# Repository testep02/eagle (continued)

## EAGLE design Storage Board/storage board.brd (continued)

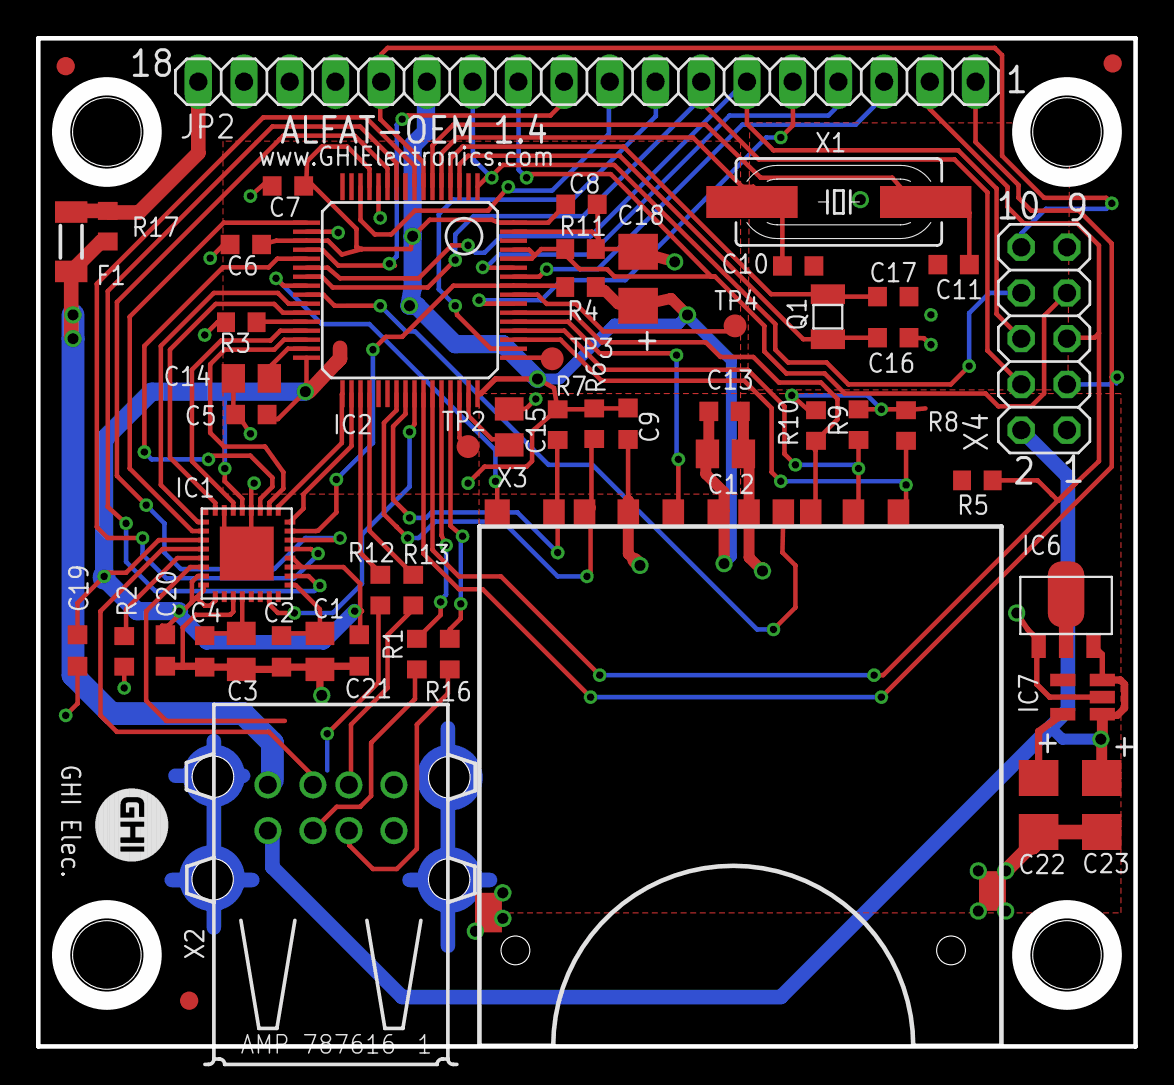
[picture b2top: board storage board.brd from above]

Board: 2 copper layers, 61.0 x 56.0 mm, 55 parts (0 on the bottom side), 59 nets.

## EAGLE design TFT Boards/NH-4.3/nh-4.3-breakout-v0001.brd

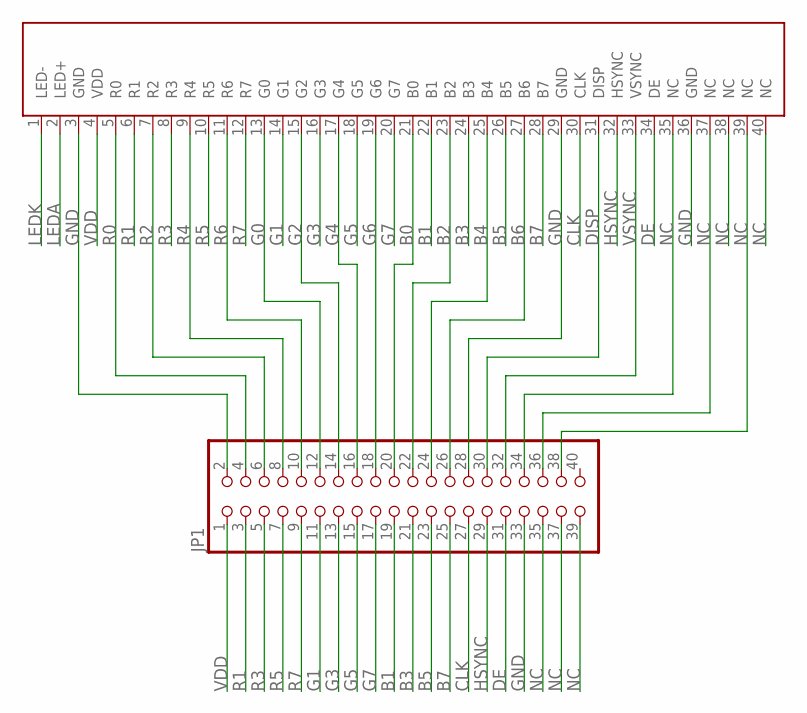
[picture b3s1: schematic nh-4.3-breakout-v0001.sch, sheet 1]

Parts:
JP1: PINHD-2X20; 2X20
U$1: NH-4.3; FPC-40

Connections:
B0: JP1.20, U$1.21 (B0)
B1: JP1.19, U$1.22 (B1)
B2: JP1.22, U$1.23 (B2)
B3: JP1.21, U$1.24 (B3)
B4: JP1.24, U$1.25 (B4)
B5: JP1.23, U$1.26 (B5)
B6: JP1.26, U$1.27 (B6)
B7: JP1.25, U$1.28 (B7)
CLK: JP1.27, U$1.30 (CLK)
DE: JP1.31, U$1.34 (DE)
DISP: JP1.30, U$1.31 (DISP)
G0: JP1.12, U$1.13 (G0)
G1: JP1.11, U$1.14 (G1)
G2: JP1.14, U$1.15 (G2)
G3: JP1.13, U$1.16 (G3)
G4: JP1.16, U$1.17 (G4)
G5: JP1.15, U$1.18 (G5)
G6: JP1.18, U$1.19 (G6)
G7: JP1.17, U$1.20 (G7)
GND: JP1.2, JP1.28, JP1.33, U$1.3 (GND), U$1.29 (GND), U$1.36 (GND); also elsewhere on the board
HSYNC: JP1.29, U$1.32 (HSYNC)
LEDA: U$1.2 (LED+); also elsewhere on the board
LEDK: U$1.1 (LED-); also elsewhere on the board
NC: JP1.34, JP1.35, JP1.36, JP1.37, JP1.38, JP1.39, U$1.35 (NC), U$1.37 (NC), U$1.38 (NC), U$1.39 (NC), U$1.40 (NC)
R0: JP1.4, U$1.5 (R0)
R1: JP1.3, U$1.6 (R1)
R2: JP1.6, U$1.7 (R2)
R3: JP1.5, U$1.8 (R3)
R4: JP1.8, U$1.9 (R4)
R5: JP1.7, U$1.10 (R5)
R6: JP1.10, U$1.11 (R6)
R7: JP1.9, U$1.12 (R7)
VDD: JP1.1, U$1.4 (VDD)
VSYNC: JP1.32, U$1.33 (VSYNC)

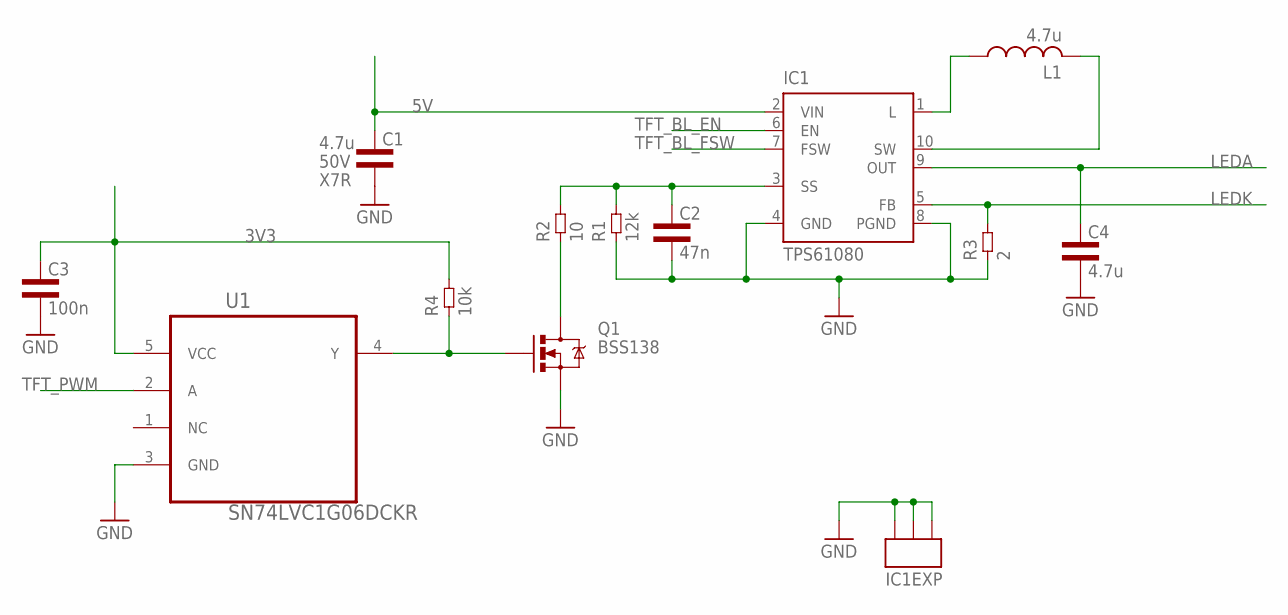
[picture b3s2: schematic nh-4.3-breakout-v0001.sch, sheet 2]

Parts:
C1: 4.7u; 1210L3; VOLTAGE 50V
C2: 47n; 0603L3
C3: 100n; 0603L3
C4: 4.7u; 1210L3
IC1: TPS61080; S-PDSO-N10
L1: 4.7u; RCL_VLCF4018-2
Q1: MOSFET-NCHANNELBSS138; SOT23
R1: 12k; 0603L3
R2: 10; 0603L3
R3: 2; 1210L3
R4: 10k; 0603L3
U1: SN74LVC1G06DCKR; SOT65P210X110-5N

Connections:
3V3: C3.P$1 (1), R4.P$2 (2), U1.5 (VCC)
5V: C1.P$1 (1), IC1.2 (VIN)
GND: C1.P$2 (2), C2.P$2 (2), C3.P$2 (2), C4.P$2 (2), IC1.4 (GND), IC1.8 (PGND), IC1.PP (EXP), IC1.PP@1 (EXP), IC1.PP@2 (EXP), Q1.2 (S), R1.P$1 (1), R3.P$1 (1), U1.3 (GND); also elsewhere on the board
LEDA: C4.P$1 (1), IC1.9 (OUT); also elsewhere on the board
LEDK: IC1.5 (FB), R3.P$2 (2); also elsewhere on the board
unnamed: C2.P$1 (1), IC1.3 (SS), R1.P$2 (2), R2.P$2 (2)
unnamed: Q1.3 (D), R2.P$1 (1)
unnamed: IC1.10 (SW), L1.2
unnamed: IC1.1 (L), L1.1
TFT_BL_EN: IC1.6 (EN)
TFT_BL_FSW: IC1.7 (FSW)
TFT_PWM: U1.2 (A)
Y: Q1.1 (G), R4.P$1 (1), U1.4 (Y)

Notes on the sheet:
BSS138

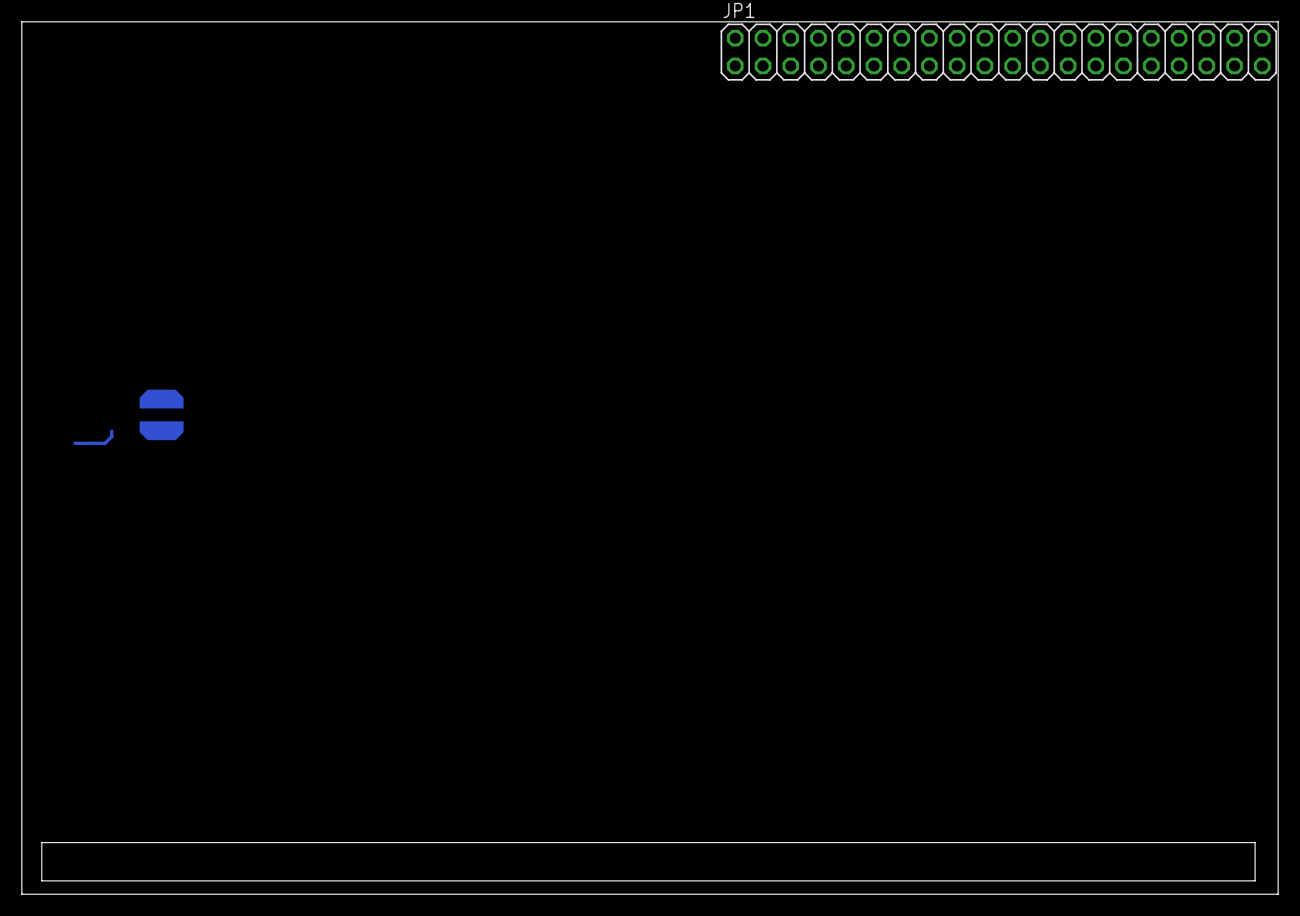
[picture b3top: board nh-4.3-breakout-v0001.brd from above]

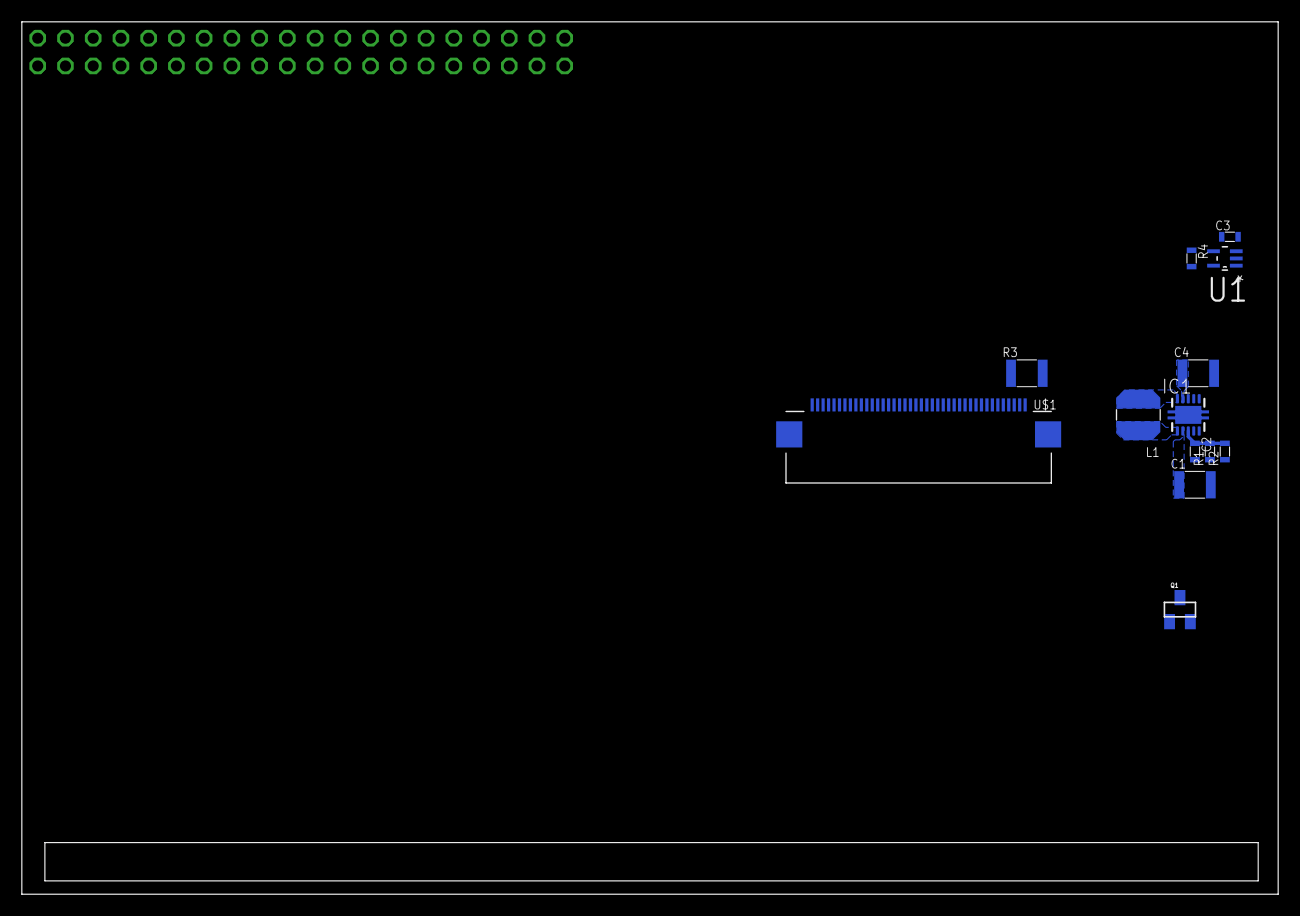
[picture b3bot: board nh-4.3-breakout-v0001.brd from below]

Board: 2 copper layers, 115.0 x 79.9 mm, 14 parts (13 on the bottom side), 41 nets.

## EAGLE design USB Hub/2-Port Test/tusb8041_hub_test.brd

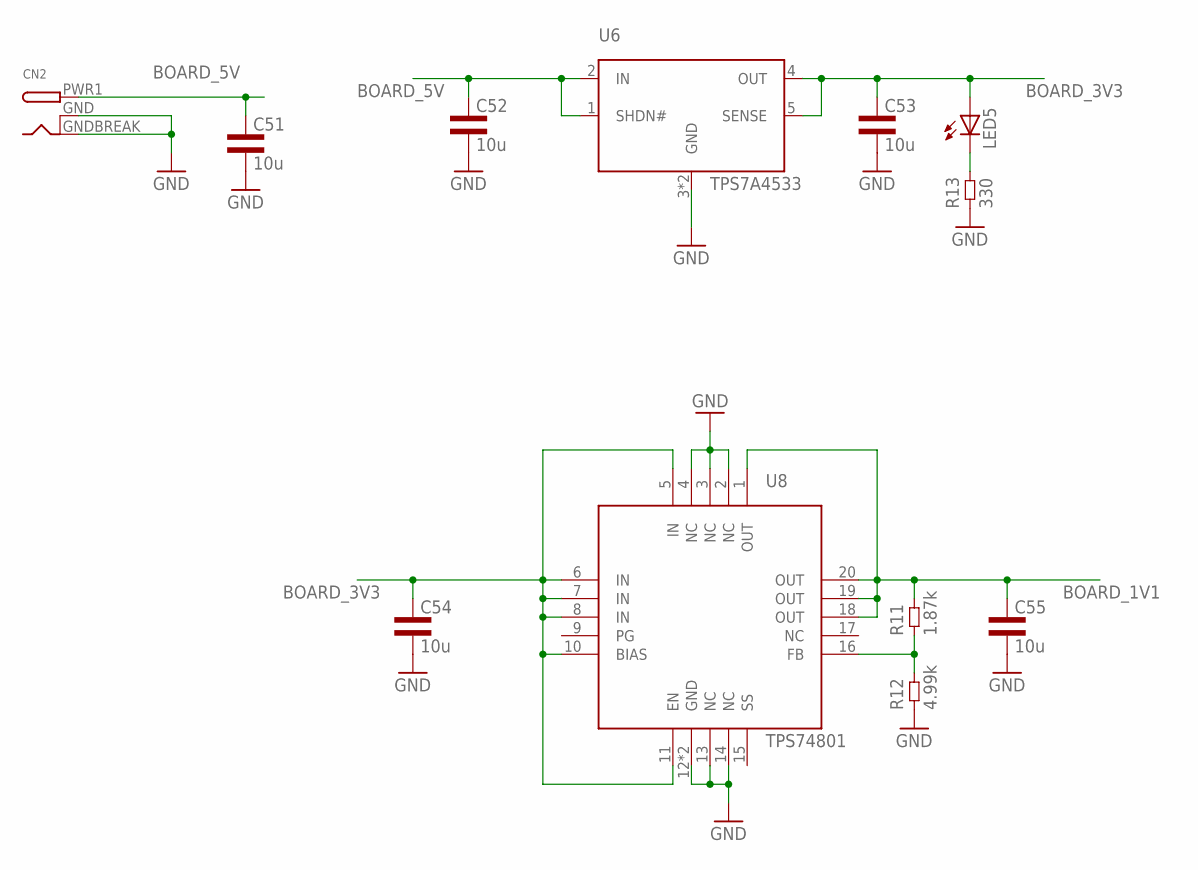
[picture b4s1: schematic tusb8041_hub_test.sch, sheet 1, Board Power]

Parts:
C51, C52, C53, C54, C55: 10u; 1206L3
CN2: DCBARRELSMT; DCJACK_2MM_SMT
LED5: LEDCHIP-LED0603; CHIP-LED0603
R11: 1.87k; 0402L3
R12: 4.99k; 0402L3
R13: 330; 0603L3
U6: TPS7A4533; R-PSFM-G5
U8: TPS74801; S-PVQFN-N20

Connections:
BOARD_1V1: C55.1, R11.P$2 (2), U8.1 (OUT), U8.18 (OUT), U8.19 (OUT), U8.20 (OUT); also elsewhere on the board
BOARD_3V3: C53.1, C54.1, LED5.A, U6.4 (OUT), U6.5 (SENSE), U8.5 (IN), U8.6 (IN), U8.7 (IN), U8.8 (IN), U8.10 (BIAS), U8.11 (EN); also elsewhere on the board
BOARD_5V: C51.1, C52.1, CN2.PWR1 (PWR), U6.1 (SHDN#), U6.2 (IN); also elsewhere on the board
GND: C51.2, C52.2, C53.2, C54.2, C55.2, CN2.GND (GNDBREAK), CN2.GNDBREAK (GND), R12.P$1 (1), R13.P$1 (1), U6.3 (GND), U6.TP (GND), U8.2 (NC), U8.3 (NC), U8.4 (NC), U8.12 (GND), U8.13 (NC), U8.14 (NC), U8.TP (GND); also elsewhere on the board
unnamed: LED5.C, R13.P$2 (2)
unnamed: R11.P$1 (1), R12.P$2 (2), U8.16 (FB)

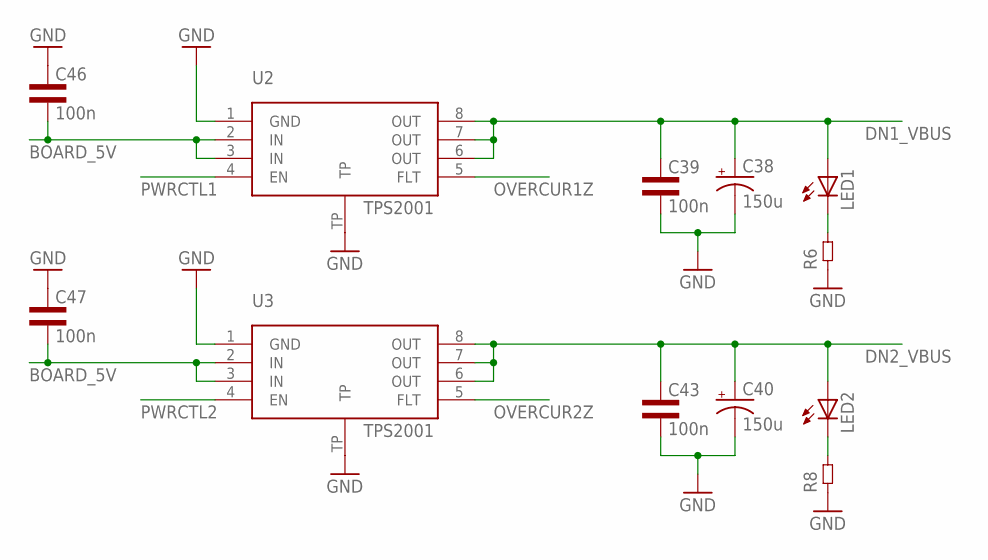
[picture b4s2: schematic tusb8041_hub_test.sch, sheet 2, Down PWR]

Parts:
C38, C40: 150u; CT7343
C39, C43, C46, C47: 100n; 0603L3
LED1, LED2: LEDCHIP-LED0603; CHIP-LED0603
R6, R8: RES0603L3; 0603L3
U2, U3: TPS2001; S-PDSO-G8

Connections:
BOARD_5V: C46.P$2 (2), C47.P$2 (2), U2.2 (IN), U2.3 (IN), U3.2 (IN), U3.3 (IN); also elsewhere on the board
DN1_VBUS: C38.+, C39.P$1 (1), LED1.A, U2.6 (OUT), U2.7 (OUT), U2.8 (OUT); also elsewhere on the board
DN2_VBUS: C40.+, C43.P$1 (1), LED2.A, U3.6 (OUT), U3.7 (OUT), U3.8 (OUT); also elsewhere on the board
GND: C38.-, C39.P$2 (2), C40.-, C43.P$2 (2), C46.P$1 (1), C47.P$1 (1), R6.P$1 (1), R8.P$1 (1), U2.1 (GND), U2.TP, U3.1 (GND), U3.TP; also elsewhere on the board
unnamed: LED1.C, R6.P$2 (2)
unnamed: LED2.C, R8.P$2 (2)
OVERCUR1Z: U2.5 (FLT); also elsewhere on the board
OVERCUR2Z: U3.5 (FLT); also elsewhere on the board
PWRCTL1: U2.4 (EN); also elsewhere on the board
PWRCTL2: U3.4 (EN); also elsewhere on the board

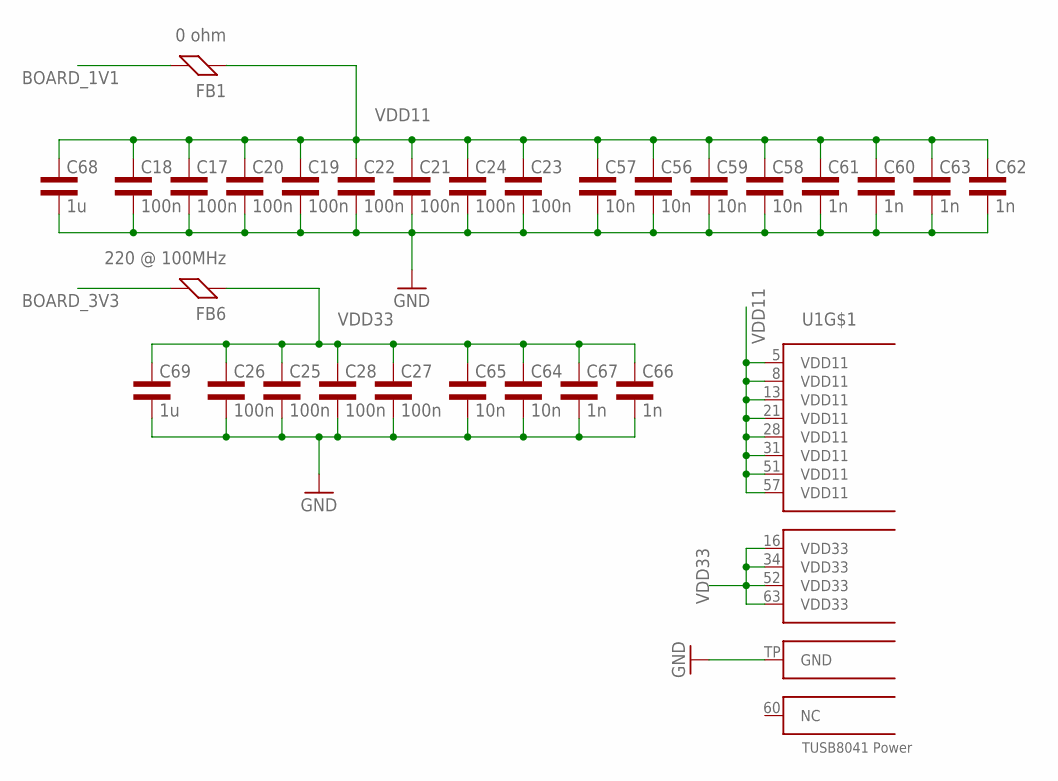
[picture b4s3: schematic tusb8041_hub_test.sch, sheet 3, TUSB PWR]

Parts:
C17, C18, C19, C20, C21, C22, C23, C24, C25, C26, C27, C28: 100n; 0402L3
C56, C57, C58, C59, C64, C65: 10n; 0402L3
C60, C61, C62, C63, C66, C67: 1n; 0402L3
C68, C69: 1u; 0805L3
FB1: 0 ohm; 0603L3
FB6: 220 @ 100MHz; 0603L3
U1: TUSB8041; VQFN64

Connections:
BOARD_1V1: FB1.P$2 (2); also elsewhere on the board
BOARD_3V3: FB6.P$2 (2); also elsewhere on the board
GND: C17.P$2 (2), C18.P$2 (2), C19.P$2 (2), C20.P$2 (2), C21.P$2 (2), C22.P$2 (2), C23.P$2 (2), C24.P$2 (2), C25.P$2 (2), C26.P$2 (2), C27.P$2 (2), C28.P$2 (2), C56.P$2 (2), C57.P$2 (2), C58.P$2 (2), C59.P$2 (2), C60.P$2 (2), C61.P$2 (2), C62.P$2 (2), C63.P$2 (2), C64.P$2 (2), C65.P$2 (2), C66.P$2 (2), C67.P$2 (2), C68.2, C69.2, U1.TP (GND); also elsewhere on the board
VDD11: C17.P$1 (1), C18.P$1 (1), C19.P$1 (1), C20.P$1 (1), C21.P$1 (1), C22.P$1 (1), C23.P$1 (1), C24.P$1 (1), C56.P$1 (1), C57.P$1 (1), C58.P$1 (1), C59.P$1 (1), C60.P$1 (1), C61.P$1 (1), C62.P$1 (1), C63.P$1 (1), C68.1, FB1.P$1 (1), U1.5 (VDD11), U1.8 (VDD11), U1.13 (VDD11), U1.21 (VDD11), U1.28 (VDD11), U1.31 (VDD11), U1.51 (VDD11), U1.57 (VDD11)
VDD33: C25.P$1 (1), C26.P$1 (1), C27.P$1 (1), C28.P$1 (1), C64.P$1 (1), C65.P$1 (1), C66.P$1 (1), C67.P$1 (1), C69.1, FB6.P$1 (1), U1.16 (VDD33), U1.34 (VDD33), U1.52 (VDD33), U1.63 (VDD33); also elsewhere on the board

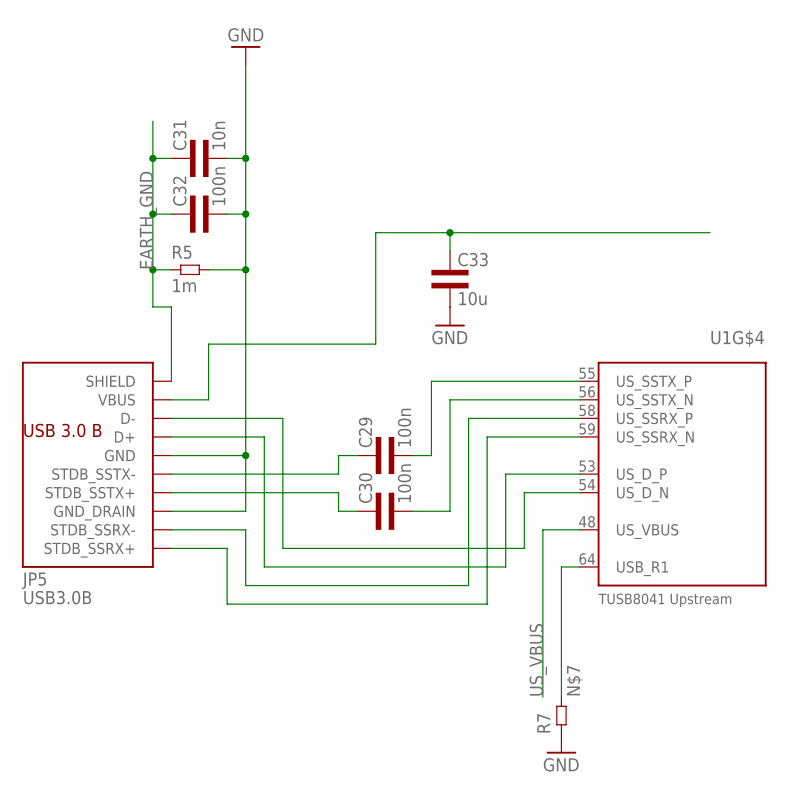
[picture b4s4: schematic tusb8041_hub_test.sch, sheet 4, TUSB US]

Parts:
C29, C30: 100n; 0402L3
C31: 10n; 0603L3
C32: 100n; 0603L3
C33: 10u; 1206L3
JP5: USB3.0B; AMPHENOLUSB3.0B
R5: 1m; 0603L3
R7: RES0402L3; 0402L3
U1: TUSB8041; VQFN64

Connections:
EARTH_GND: C31.P$1 (1), C32.P$1 (1), JP5.10@1 (SHIELD), JP5.10@2 (SHIELD), R5.P$1 (1); also elsewhere on the board
GND: C31.P$2 (2), C32.P$2 (2), C33.2, JP5.4 (GND), JP5.7 (GND_DRAIN), R5.P$2 (2), R7.P$1 (1); also elsewhere on the board
unnamed: R7.P$2 (2), U1.64 (USB_R1)
US_CAP_SSTX_N: C29.P$1 (1), JP5.5 (STDB_SSTX-)
US_CAP_SSTX_P: C30.P$1 (1), JP5.6 (STDB_SSTX+)
US_D_N: JP5.2 (D-), U1.54 (US_D_N)
US_D_P: JP5.3 (D+), U1.53 (US_D_P)
US_SSRX_N: JP5.9 (STDB_SSRX+), U1.59 (US_SSRX_N)
US_SSRX_P: JP5.8 (STDB_SSRX-), U1.58 (US_SSRX_P)
US_SSTX_N: C30.P$2 (2), U1.56 (US_SSTX_N)
US_SSTX_P: C29.P$2 (2), U1.55 (US_SSTX_P)
US_VBUS: C33.1, JP5.1 (VBUS), U1.48 (US_VBUS)

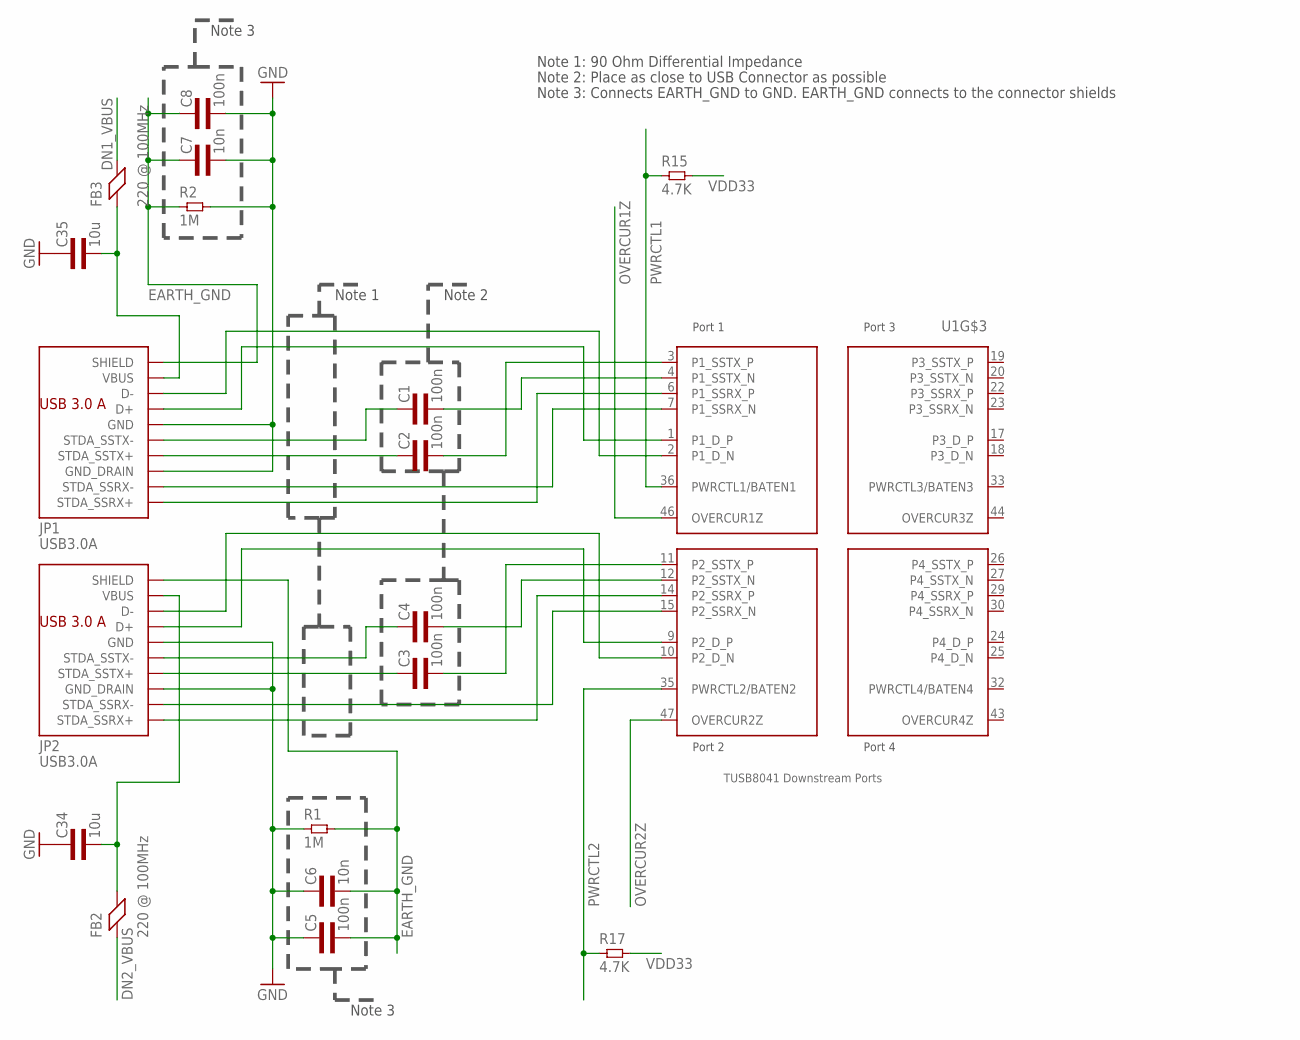
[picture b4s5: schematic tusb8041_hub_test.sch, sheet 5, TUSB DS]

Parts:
C1, C2, C3, C4: 100n; 0402L3
C5, C8: 100n; 0603L3
C6, C7: 10n; 0603L3
C34, C35: 10u; 1206L3
FB2, FB3: 220 @ 100MHz; 0603L1
JP1, JP2: USB3.0A; AMPHENOLUSB3.0A
R1, R2: 1M; 0603L3
R15, R17: 4.7K; 0402L3
U1: TUSB8041; VQFN64

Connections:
DN1_VBUS: FB3.2; also elsewhere on the board
DN2_VBUS: FB2.1; also elsewhere on the board
EARTH_GND: C5.P$2 (2), C6.P$2 (2), C7.P$1 (1), C8.P$1 (1), JP1.10@1 (SHIELD), JP1.10@2 (SHIELD), JP2.10@1 (SHIELD), JP2.10@2 (SHIELD), R1.P$2 (2), R2.P$1 (1); also elsewhere on the board
GND: C5.P$1 (1), C6.P$1 (1), C7.P$2 (2), C8.P$2 (2), C34.1, C35.1, JP1.4 (GND), JP1.7 (GND_DRAIN), JP2.4 (GND), JP2.7 (GND_DRAIN), R1.P$1 (1), R2.P$2 (2); also elsewhere on the board
unnamed: C35.2, FB3.1, JP1.1 (VBUS)
unnamed: C34.2, FB2.2, JP2.1 (VBUS)
OVERCUR1Z: U1.46 (OVERCUR1Z); also elsewhere on the board
OVERCUR2Z: U1.47 (OVERCUR2Z); also elsewhere on the board
P1_CAP_SSTX_N: C1.P$1 (1), JP1.8 (STDA_SSTX-)
P1_CAP_SSTX_P: C2.P$1 (1), JP1.9 (STDA_SSTX+)
P1_D_N: JP1.2 (D-), U1.2 (P1_D_N)
P1_D_P: JP1.3 (D+), U1.1 (P1_D_P)
P1_SSRX_N: JP1.5 (STDA_SSRX-), U1.7 (P1_SSRX_N)
P1_SSRX_P: JP1.6 (STDA_SSRX+), U1.6 (P1_SSRX_P)
P1_SSTX_N: C1.P$2 (2), U1.4 (P1_SSTX_N)
P1_SSTX_P: C2.P$2 (2), U1.3 (P1_SSTX_P)
P2_CAP_SSTX_N: C4.P$1 (1), JP2.8 (STDA_SSTX-)
P2_CAP_SSTX_P: C3.P$1 (1), JP2.9 (STDA_SSTX+)
P2_D_N: JP2.2 (D-), U1.10 (P2_D_N)
P2_D_P: JP2.3 (D+), U1.9 (P2_D_P)
P2_SSRX_N: JP2.5 (STDA_SSRX-), U1.15 (P2_SSRX_N)
P2_SSRX_P: JP2.6 (STDA_SSRX+), U1.14 (P2_SSRX_P)
P2_SSTX_N: C4.P$2 (2), U1.12 (P2_SSTX_N)
P2_SSTX_P: C3.P$2 (2), U1.11 (P2_SSTX_P)
PWRCTL1: R15.P$1 (1), U1.36 (PWRCTL1/BATEN1); also elsewhere on the board
PWRCTL2: R17.P$1 (1), U1.35 (PWRCTL2/BATEN2); also elsewhere on the board
VDD33: R15.P$2 (2), R17.P$2 (2); also elsewhere on the board

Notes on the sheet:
Note 1
Note 2
Note 3
Note 1: 90 Ohm Differential Impedance
Note 2: Place as close to USB Connector as possible
Note 3: Connects EARTH_GND to GND. EARTH_GND connects to the connector shields

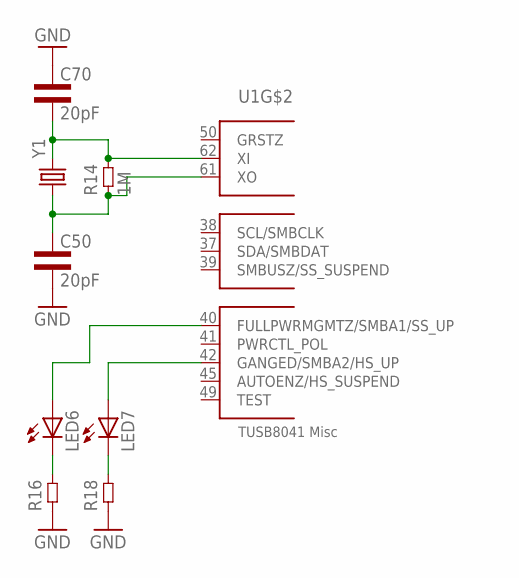
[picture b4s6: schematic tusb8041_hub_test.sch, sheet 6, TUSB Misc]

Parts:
C50, C70: 20pF; 0402L3
LED6, LED7: LEDCHIPLED_0603; CHIPLED_0603
R14: 1M; 0402L3
R16, R18: RES0402L3; 0402L3
U1: TUSB8041; VQFN64
Y1: CRYSTALHC49US; HC49US

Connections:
CLK_N: C70.P$2 (2), R14.P$2 (2), U1.62 (XI), Y1.2
CLK_P: C50.P$1 (1), R14.P$1 (1), U1.61 (XO), Y1.1
GND: C50.P$2 (2), C70.P$1 (1), R16.P$1 (1), R18.P$1 (1); also elsewhere on the board
unnamed: LED6.C, R16.P$2 (2)
unnamed: LED7.C, R18.P$2 (2)
unnamed: LED7.A, U1.42 (GANGED/SMBA2/HS_UP)
unnamed: LED6.A, U1.40 (FULLPWRMGMTZ/SMBA1/SS_UP)

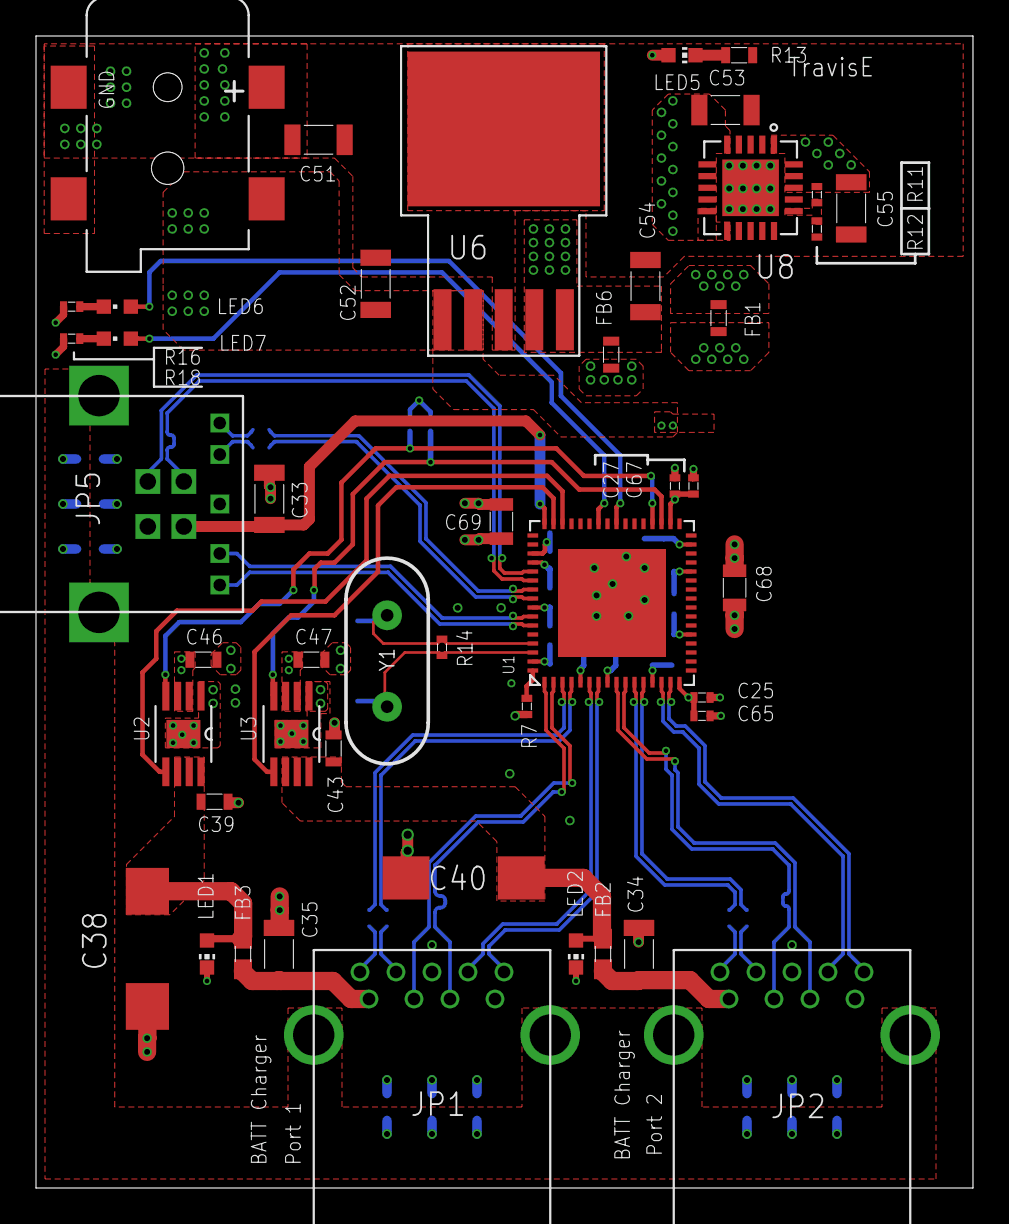
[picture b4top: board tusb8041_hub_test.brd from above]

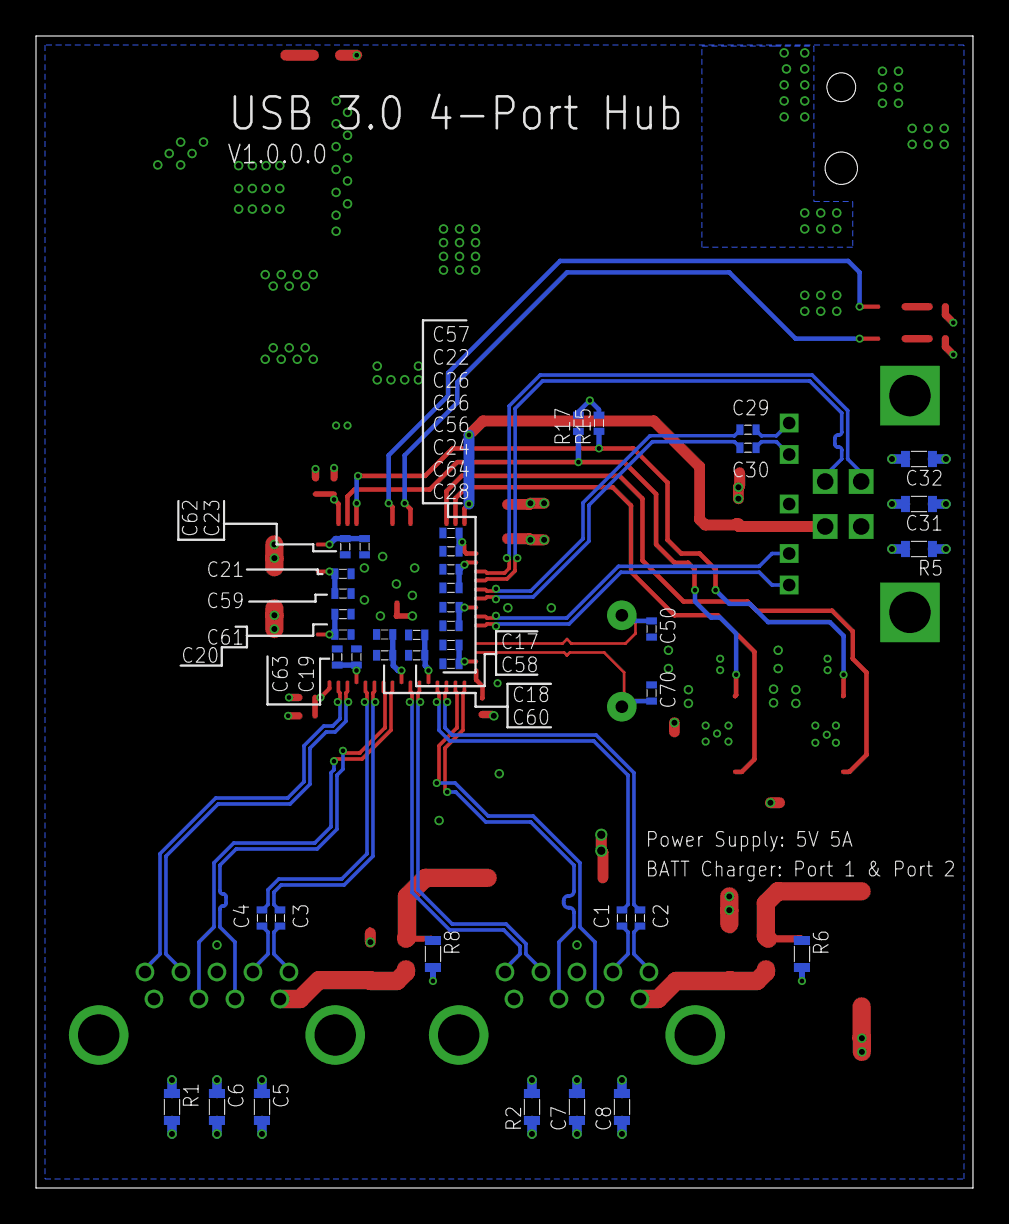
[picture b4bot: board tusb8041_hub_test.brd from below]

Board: 4 copper layers, 52.1 x 64.0 mm, 87 parts (41 on the bottom side), 51 nets.

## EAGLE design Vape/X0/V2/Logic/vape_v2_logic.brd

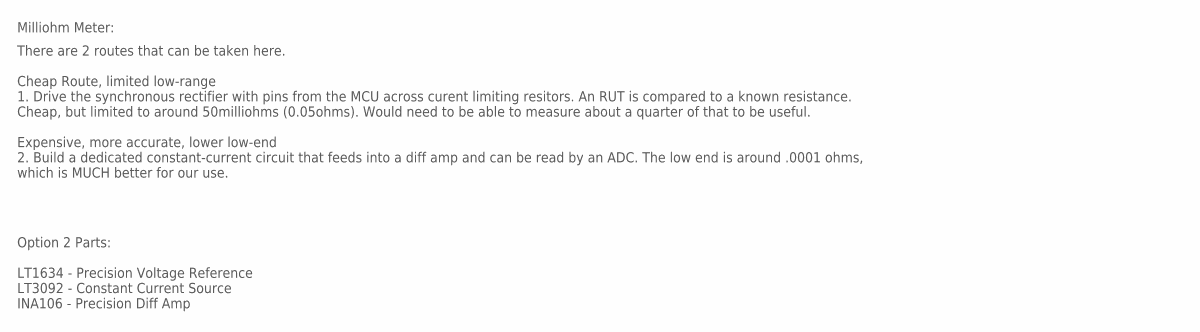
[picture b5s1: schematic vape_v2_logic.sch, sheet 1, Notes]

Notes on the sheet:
Milliohm Meter:
There are 2 routes that can be taken here. Cheap Route, limited low-range 1. Drive the synchronous rectifier with pins from the MCU across curent limiting resitors. An RUT is compared to a known resistance. Cheap, but limited to around 50milliohms (0.05ohms). Would need to be able to measure about 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
Option 2 Parts: LT1634 - Precision Voltage Reference LT3092 - Constant Current Source INA106 - Precision Diff Amp

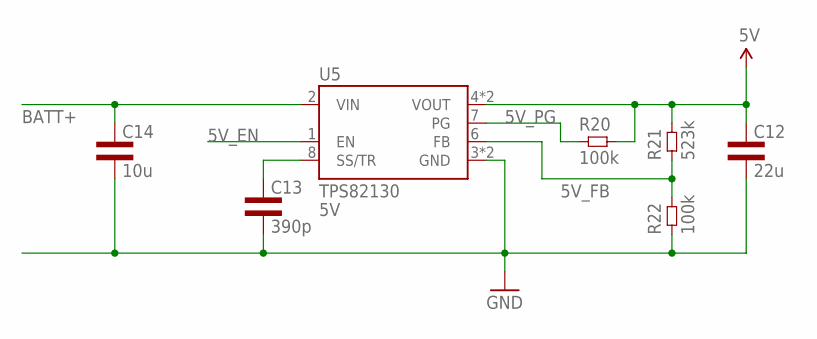
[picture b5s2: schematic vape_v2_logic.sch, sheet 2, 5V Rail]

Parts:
C12: 22u; 1206L3
C13: 390p; 0603L3
C14: 10u; 0805L3
R20: 100k; 0805L3
R21: 523k; 0603L3
R22: 100k; 0603L3
U5: TPS82130; SIL0008D

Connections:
5V: C12.1, R20.2, R21.P$2 (2), U5.4 (VOUT), U5.5 (VOUT)
5V_EN: U5.1 (EN)
5V_FB: R21.P$1 (1), R22.P$2 (2), U5.6 (FB)
5V_PG: R20.1, U5.7 (PG)
5V_SS: C13.P$1 (1), U5.8 (SS/TR)
BATT+: C14.1, U5.2 (VIN); also elsewhere on the board
GND: C12.2, C13.P$2 (2), C14.2, R22.P$1 (1), U5.3 (GND), U5.TP (GND); also elsewhere on the board

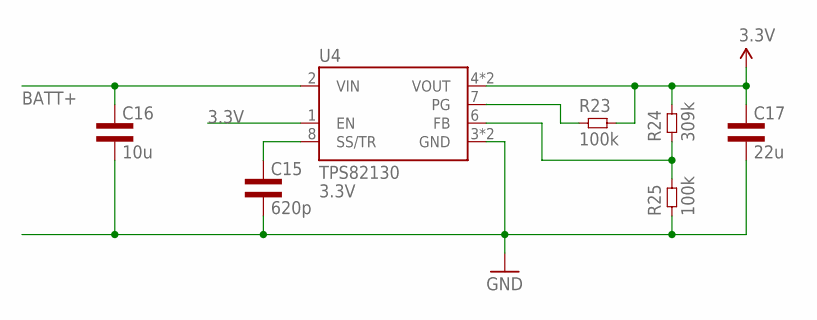
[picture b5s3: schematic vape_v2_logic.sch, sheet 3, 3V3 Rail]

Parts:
C15: 620p; 0603L3
C16: 10u; 0805L3
C17: 22u; 1206L3
R23: 100k; 0805L3
R24: 309k; 0603L3
R25: 100k; 0603L3
U4: TPS82130; SIL0008D

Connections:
3.3V: C17.1, R23.2, R24.P$2 (2), U4.1 (EN), U4.4 (VOUT), U4.5 (VOUT); also elsewhere on the board
BATT+: C16.1, U4.2 (VIN); also elsewhere on the board
GND: C15.P$2 (2), C16.2, C17.2, R25.P$1 (1), U4.3 (GND), U4.TP (GND); also elsewhere on the board
unnamed: R23.1, U4.7 (PG)
unnamed: R24.P$1 (1), R25.P$2 (2), U4.6 (FB)
unnamed: C15.P$1 (1), U4.8 (SS/TR)

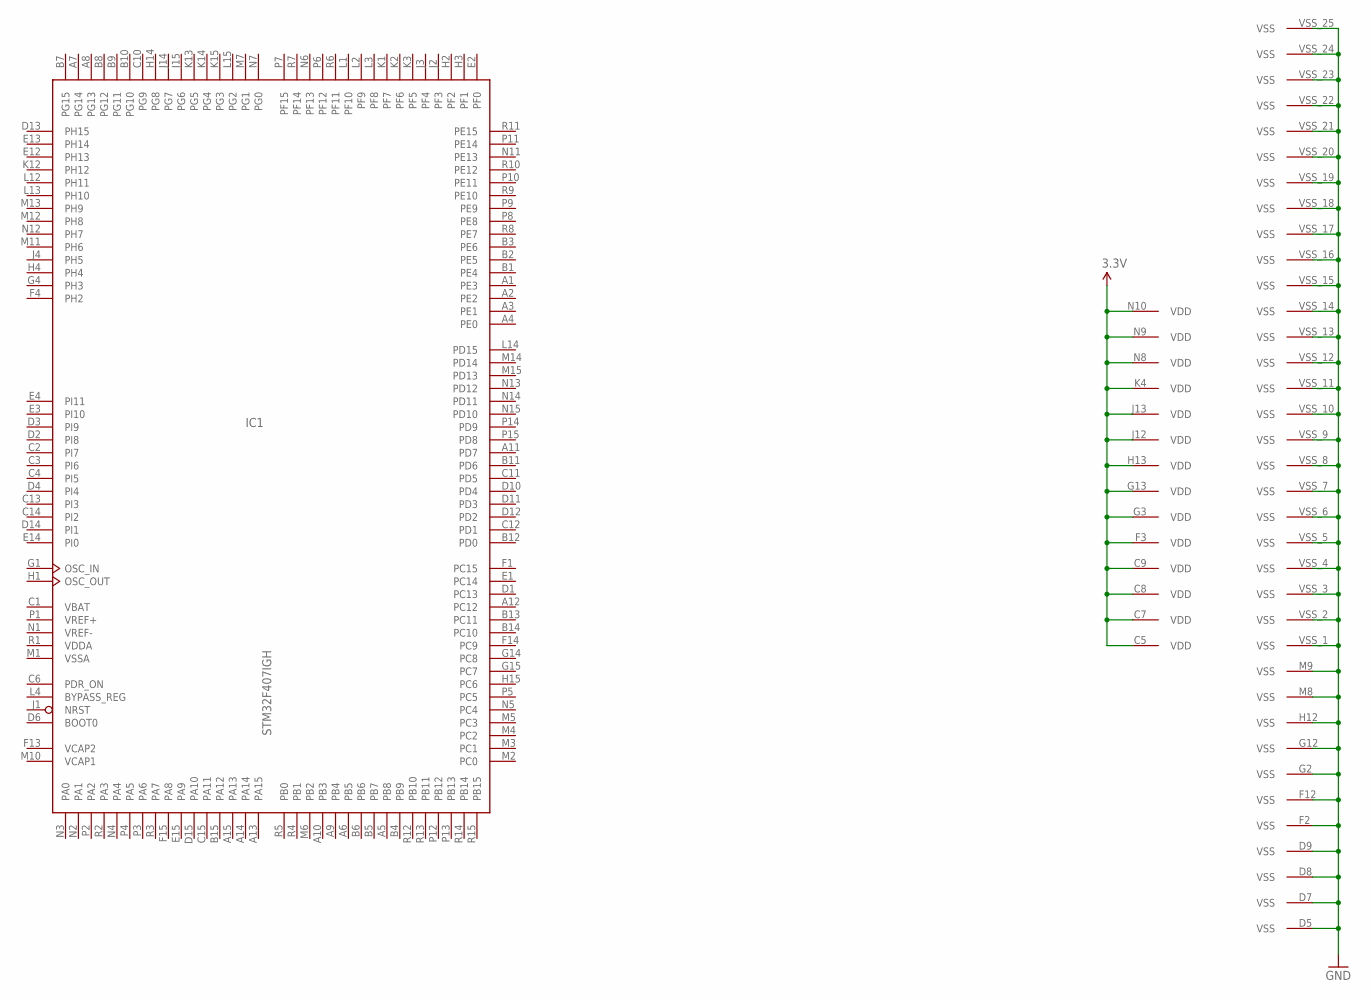
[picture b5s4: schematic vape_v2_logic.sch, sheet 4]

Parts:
IC1: STM32F407IGH; UFBGA176+25

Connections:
3.3V: IC1.C5 (VDD), IC1.C7 (VDD), IC1.C8 (VDD), IC1.C9 (VDD), IC1.F3 (VDD), IC1.G3 (VDD), IC1.G13 (VDD), IC1.H13 (VDD), IC1.J12 (VDD), IC1.J13 (VDD), IC1.K4 (VDD), IC1.N8 (VDD), IC1.N9 (VDD), IC1.N10 (VDD); also elsewhere on the board
GND: IC1.D5 (VSS), IC1.D7 (VSS), IC1.D8 (VSS), IC1.D9 (VSS), IC1.F2 (VSS), IC1.F12 (VSS), IC1.G2 (VSS), IC1.G12 (VSS), IC1.H12 (VSS), IC1.M8 (VSS), IC1.M9 (VSS), IC1.VSS_1 (VSS), IC1.VSS_2 (VSS), IC1.VSS_3 (VSS), IC1.VSS_4 (VSS), IC1.VSS_5 (VSS), IC1.VSS_6 (VSS), IC1.VSS_7 (VSS), IC1.VSS_8 (VSS), IC1.VSS_9 (VSS), IC1.VSS_10 (VSS), IC1.VSS_11 (VSS), IC1.VSS_12 (VSS), IC1.VSS_13 (VSS), IC1.VSS_14 (VSS), IC1.VSS_15 (VSS), IC1.VSS_16 (VSS), IC1.VSS_17 (VSS), IC1.VSS_18 (VSS), IC1.VSS_19 (VSS), IC1.VSS_20 (VSS), IC1.VSS_21 (VSS), IC1.VSS_22 (VSS), IC1.VSS_23 (VSS), IC1.VSS_24 (VSS), IC1.VSS_25 (VSS); also elsewhere on the board
VBAT: IC1.C1 (VBAT)
VCAP1: IC1.M10 (VCAP1)
VCAP2: IC1.F13 (VCAP2)
VDDA: IC1.R1 (VDDA)
VREF+: IC1.P1 (VREF+)
VREF-: IC1.N1 (VREF-)
VSSA: IC1.M1 (VSSA)
